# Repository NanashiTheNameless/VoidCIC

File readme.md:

# VoidCIC

## VoidCIC is a fork of the original [NullCIC](<https://github.com/Redherring32/NullCIC/>)

A little board to replace the CIC on the Original NES or [OpenTendo](<https://github.com/Redherring32/OpenTendo>), and restore reset functionality.

All the files needed to make your own are located in the [Production folder](<production>).

It is also for sale on my [Tindie](<https://www.tindie.com/products/37068/>) for those who dont wanna make it themselves, or those who want to support me!

You can also do the same thing that NullCIC/VoidCIC does manually, just check ["Reset fix without NullCIC(VoidCIC).jpg"](<Reset fix without NullCIC(VoidCIC).jpg>) for instructions!

## Credits

Original by [Redherring32](<https://github.com/Redherring32>), they did most (if not all) if the theoretical design and hard work!

VoidCIC is a fork of by [NullCIC](<https://github.com/Redherring32/NullCIC/>). VoidCIC is made and maintaned by [NanashiTheNameless/NamelessNanashi](<https://gh.NamelessNanashi.dev/>).

All of the [git contributors](<https://github.com/NanashiTheNameless/VoidCIC/graphs/contributors>).

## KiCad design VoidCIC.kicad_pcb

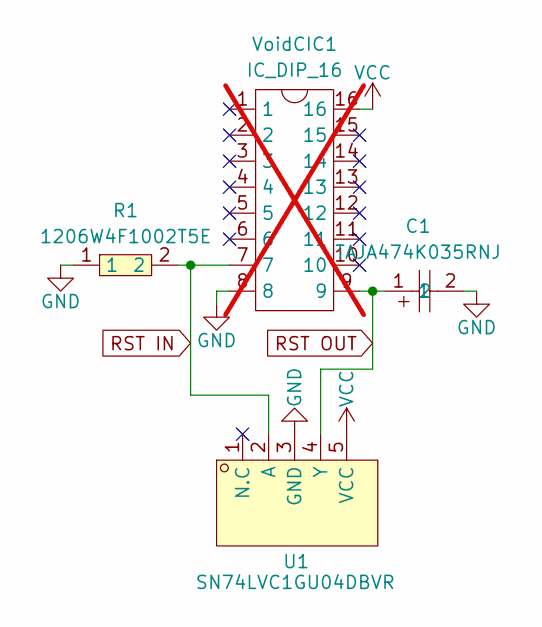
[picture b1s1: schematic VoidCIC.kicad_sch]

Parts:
C1: TAJA474K035RNJ; CAP-SMD_L3.2-W1.6-RD; LCSC Part C11368
R1: 1206W4F1002T5E; R1206; LCSC Part C17902
U1: SN74LVC1GU04DBVR; SOT-23-5_L3.0-W1.7-P0.95-LS2.8-BR; LCSC Part C81934
VoidCIC1: IC_DIP_16; DIP-16_W7.62mm_LongPads; LCSC Part C6332201; not fitted

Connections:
GND: C1.2, R1.1, U1.3 (GND), VoidCIC1.8
RST IN: R1.2, U1.2 (A), VoidCIC1.7
RST OUT: C1.1, U1.4 (Y), VoidCIC1.9
VCC: U1.5 (VCC), VoidCIC1.16

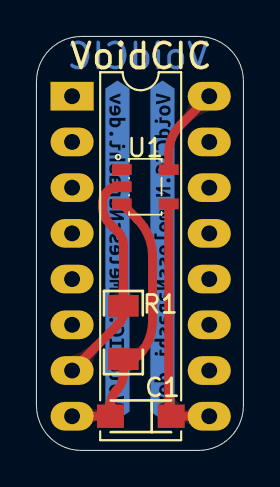
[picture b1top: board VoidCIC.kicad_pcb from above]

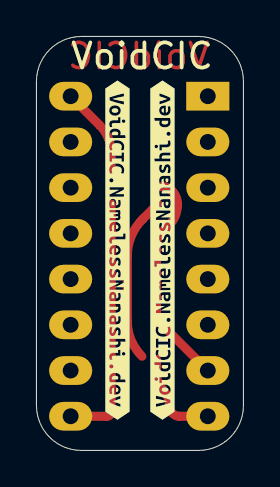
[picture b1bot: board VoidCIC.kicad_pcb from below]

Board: 2 copper layers, 11.5 x 23.0 mm, 8 parts (4 on the bottom side), 4 nets.

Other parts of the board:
kibuzzard-675A635B, kibuzzard-675A635B#2: G***; kibuzzard-675A635B
kibuzzard-675A6399, kibuzzard-675A6399#2: G***; kibuzzard-675A6399

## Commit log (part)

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2024-12-12 Make initial overhaul
2024-12-12 [ImgBot] Optimize images
    *Total -- 1,905.27kb -> 1,512.21kb (20.63%)
    /Reset fix without NullCIC(VoidCIC).jpg -- 1,863.79kb -> 1,476.44kb (20.78%)
    /VoidCIC.png -- 41.48kb -> 35.77kb (13.76%)
2024-12-12 Fix a silkscreen DFM error
2024-12-12 add image optimizer workflows
2024-12-12 Compressed Images
2024-12-12 update production files
2024-12-12 update production files again
2024-12-12 update kicad model and add blender render
2024-12-12 Round tracks.
2024-12-13 MAJOR FIX: Repair Schematic to actually be correct now, Redherring32's schematic was a nightmare so I double checked the board and noticed this issue.
2024-12-14 update pcb and sch locations
2024-12-15 update production files to make soldering to easier
2024-12-15 update render
2025-01-08 update files to fix overly tight pin fit, its functional without but better this way
2025-01-08 Increase hole size more and round board to make the fixed version more apparent and hopefully make it look better
2025-01-08 [ImgBot] Optimize images
    /VoidCIC.png -- 56.58kb -> 46.03kb (18.64%)
2025-01-09 Add links to the Tindie!
2025-01-21 Update readme.md for clarity
2025-06-03 update to kicad 9
2025-06-09 update production after linting
2025-06-09 more lint
